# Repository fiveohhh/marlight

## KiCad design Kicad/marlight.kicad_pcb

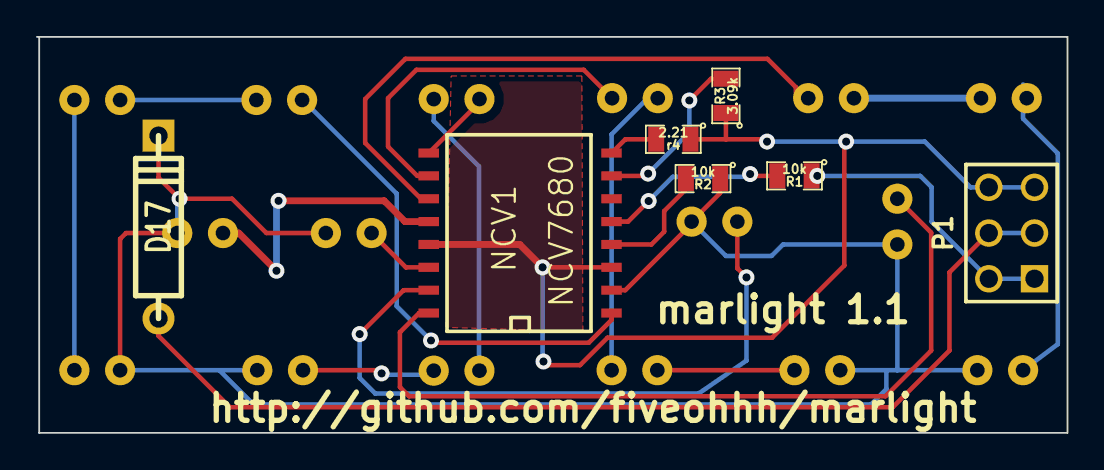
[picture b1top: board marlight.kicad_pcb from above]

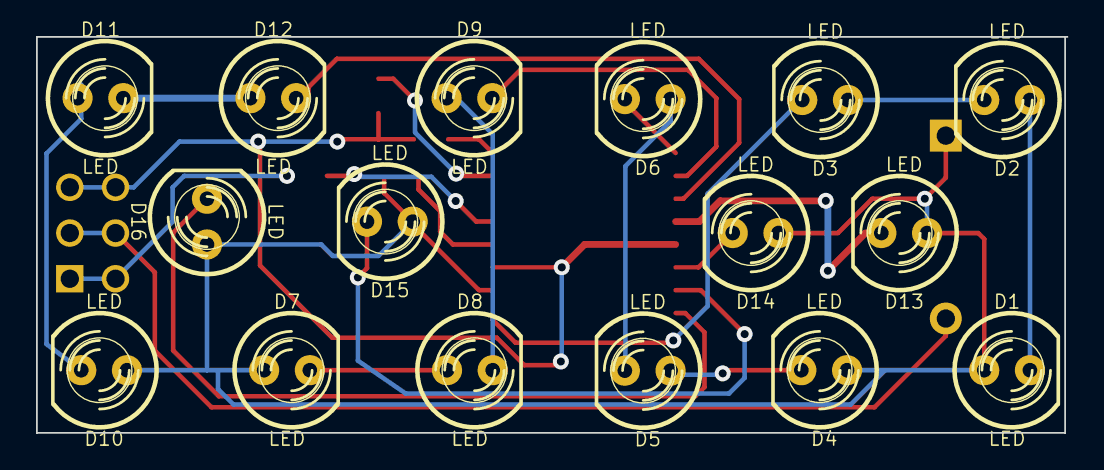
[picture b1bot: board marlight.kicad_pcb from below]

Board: 2 copper layers, 57.3 x 22.0 mm, 23 parts (16 on the bottom side), 24 nets.

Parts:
D1, D2, D3, D4, D5, D6, D7, D8, D9, D10, D11, D12, D13, D14, D15, D16: LED; LED-5MM
D17: DIODE; D4
NCV1: NCV7680; SO16W
P1: CONN_3X2; pin_array_3x2
R1, R2: 10k; SM0805
R3: 3.09k; SM0805
r4: 2.21; SM0805

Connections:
GND: NCV1.3, NCV1.13, P1.5, P1.6, R3.1, r4.1
unnamed: D14.2, NCV1.14
unnamed: D15.2, NCV1.15
unnamed: P1.1, P1.2, R1.1
unnamed: D16.2, NCV1.16
unnamed: D13.2, NCV1.12
unnamed: D6.2, NCV1.9
unnamed: D17.1, P1.3, P1.4
unnamed: D3.2, NCV1.1
unnamed: NCV1.5, R1.2
unnamed: NCV1.7, R3.2
unnamed: D12.2, NCV1.11
unnamed: D1.2, D2.1
unnamed: D4.2, D5.1
unnamed: D7.2, D8.1
unnamed: D10.2, D11.1
unnamed: D2.2, D3.1
unnamed: D5.2, D6.1
unnamed: D8.2, D9.1
unnamed: D11.2, D12.1
unnamed: D9.2, NCV1.10
unnamed: D1.1, D4.1, D7.1, D10.1, D13.1, D14.1, D15.1, D16.1, D17.2, NCV1.2, R2.1
unnamed: NCV1.4, R2.2
unnamed: NCV1.8, r4.2

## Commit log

2014-10-10 initial blinker work
2014-11-13 Audit test
2014-11-13 fixes
2014-11-13 another
2015-02-12 Adding Kicad files
2015-05-28 added voltage stuff and some other fixes
    Not tested in the slightest, not even ran on hardware
